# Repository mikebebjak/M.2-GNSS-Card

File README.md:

There are plenty of USB GNSS modules but very few M.2 modules for PCs. This project sought to rectify this issue by using a u-Blox M8C chip on a M.2 card. This way you can add GNSS to any PC when customers do not want to use external USB dongles. 
This card uses an HF4 antenna header for an external antenna (either direct or through a converter cable).
You can also download u-Blox software to test it out in Windows, as the attached screenshot shows.
Hopefully this helps someone!

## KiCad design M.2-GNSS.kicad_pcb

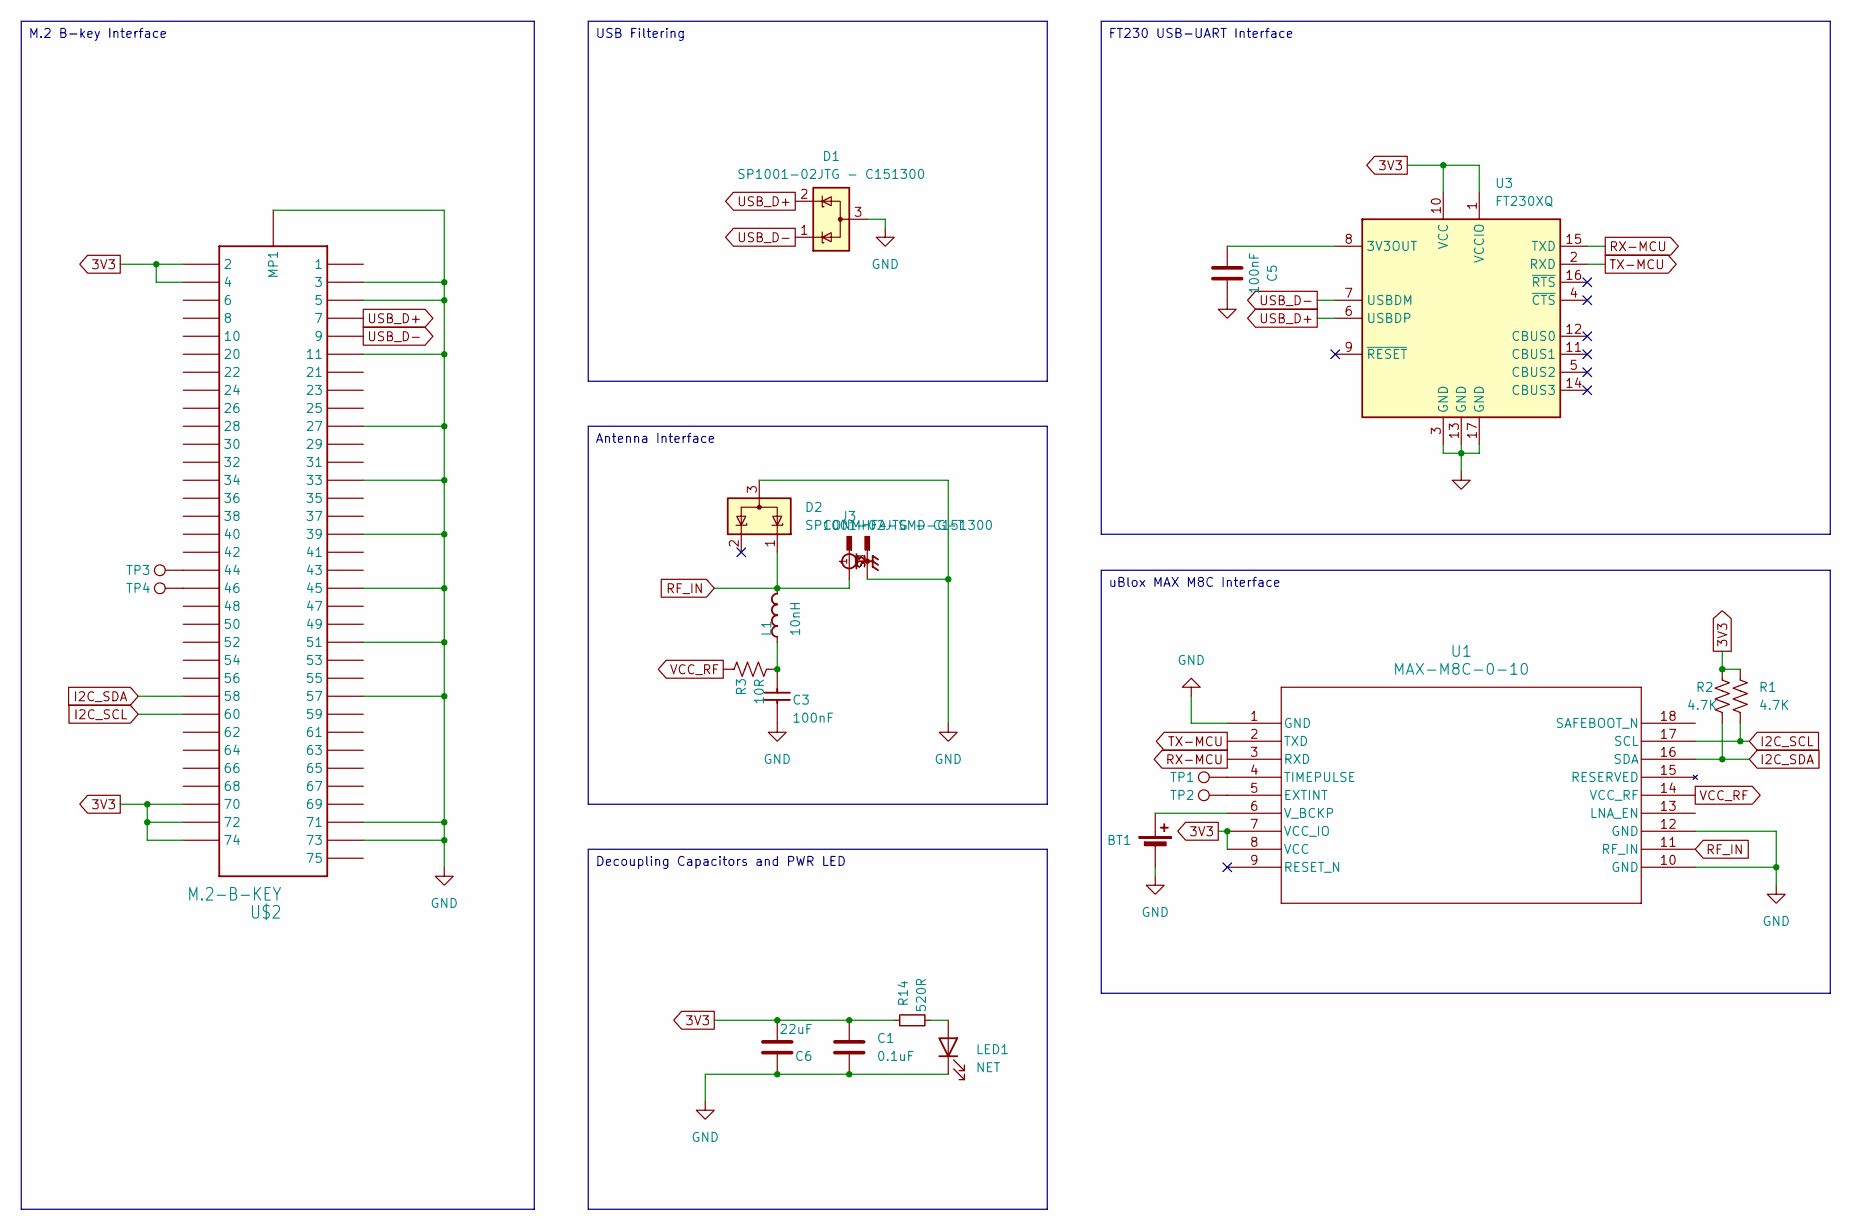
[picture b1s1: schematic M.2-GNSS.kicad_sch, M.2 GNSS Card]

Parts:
BT1: Battery_Cell; BAT_3030TR
C1: 0.1uF; C_0402_1005Metric
C3: 100nF; C_0402_1005Metric; PART NUMBER C0402-0.8p
C5: 100nF; C_0402_1005Metric
C6: 22uF; C_0603_1608Metric
D1, D2: SP1001-02JTG - C151300; SOT-323_SC-70
J3: CONMHF4-SMD-G-T; LINX_CONMHF4-SMD-G-T
L1: 10nH; C_0402_1005Metric_Pad0.74x0.62mm_HandSolder; PART NUMBER L0402-4n7
LED1: NET; LED_0402_1005Metric
R1, R2: 4.7K; R_0402_1005Metric
R3: 10R; R_0402_1005Metric
R14: 520R; R_0402_1005Metric
TP1: TIMEPULSE; TestPoint_Pad_D1.5mm
TP2: EXTINT; TestPoint_Pad_D1.5mm
TP3: GPIO2; TestPoint_Pad_D1.5mm
TP4: GPIO3; TestPoint_Pad_D1.5mm
U1: MAX-M8C-0-10; MAX-8&slash_MAX-M8_UBL
U3: FT230XQ; QFN-16-1EP_4x4mm_P0.65mm_EP2.1x2.1mm
U$2: M.2-B-KEY

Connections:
3V3: C1.2, C6.1, R1.1, R2.1, R14.1, U1.7 (VCC_IO), U1.8 (VCC), U3.1 (VCCIO), U3.10 (VCC), U$2.P$2 (2), U$2.P$4 (4), U$2.P$70 (70), U$2.P$72 (72), U$2.P$74 (74)
GND: BT1.2 (-), C1.1, C3.1, C5.1, C6.2, D1.3 (A), D2.3 (A), J3.S1, J3.S2, J3.S3, LED1.1 (K), U1.1 (GND), U1.10 (GND), U1.12 (GND), U3.3 (GND), U3.13 (GND), U3.17 (GND), U$2.MOUNTING-HOLE (MP1), U$2.P$3 (3), U$2.P$5 (5), U$2.P$11 (11), U$2.P$27 (27), U$2.P$33 (33), U$2.P$39 (39), U$2.P$45 (45), U$2.P$51 (51), U$2.P$57 (57), U$2.P$71 (71), U$2.P$73 (73); also elsewhere on the board
I2C_SCL: R1.2, U1.17 (SCL), U$2.P$60 (60)
I2C_SDA: R2.2, U1.16 (SDA), U$2.P$58 (58)
unnamed: BT1.1 (+), U1.6 (V_BCKP)
unnamed: C3.2, L1.1, R3.2
unnamed: LED1.2 (A), R14.2
unnamed: TP2.1, U1.5 (EXTINT)
unnamed: TP1.1, U1.4 (TIMEPULSE)
unnamed: C5.2, U3.8 (3V3OUT)
unnamed: TP3.1, U$2.P$44 (44)
unnamed: TP4.1, U$2.P$46 (46)
RF_IN: D2.1 (K), J3.1, L1.2, U1.11 (RF_IN); also elsewhere on the board
RX-MCU: U1.3 (RXD), U3.15 (TXD)
TX-MCU: U1.2 (TXD), U3.2 (RXD)
USB_D+: D1.2 (K), U3.6 (USBDP), U$2.P$7 (7)
USB_D-: D1.1 (K), U3.7 (USBDM), U$2.P$9 (9)
VCC_RF: R3.1, U1.14 (VCC_RF)

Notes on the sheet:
FT230 USB-UART Interface
Antenna Interface
M.2 B-key Interface
Decoupling Capacitors and PWR LED
USB Filtering
uBlox MAX M8C Interface

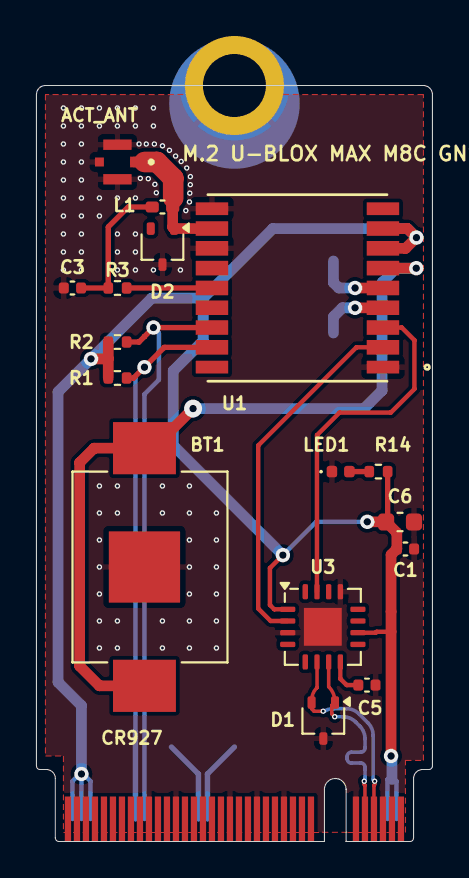
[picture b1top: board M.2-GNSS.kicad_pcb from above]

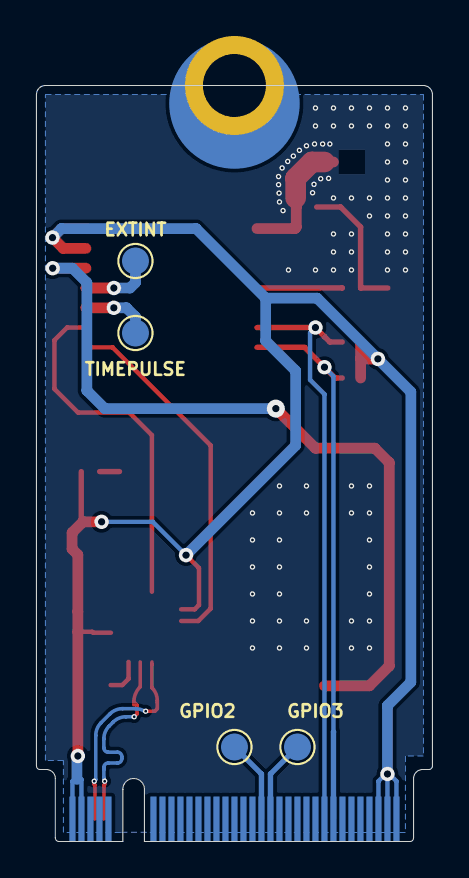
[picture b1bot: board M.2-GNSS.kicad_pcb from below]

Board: 2 copper layers, 22.0 x 42.0 mm, 21 parts (4 on the bottom side), 18 nets.

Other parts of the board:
ACT_ANT: CONMHF4-SMD-G-T; LINX_CONMHF4-SMD-G-T

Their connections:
GND: ACT_ANT.S1, ACT_ANT.S2, ACT_ANT.S3; also elsewhere on the board
RF_IN: ACT_ANT.1; also elsewhere on the board

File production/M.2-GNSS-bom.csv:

Comment,Designator,Footprint,JLCPCB Part #
SP1001-02JTG,"D1,D2",SOT-323_SC-70,C151300
FT230XQ,U3,QFN-16-1EP_4x4mm_P0.65mm_EP2.1x2.1mm,C128629
100nF,"C5,C3",C_0402_1005Metric,C1525 
Battery_Cell,BT1,BAT_3030TR,
520R,R14,R_0402_1005Metric,C365029
NET,LED1,LED_0402_1005Metric,
10R,R3,R_0402_1005Metric,
4.7K,"R2,R1",R_0402_1005Metric,
22uF,C6,C_0603_1608Metric,
0.1uF,C1,C_0402_1005Metric,C1525 
10nH,L1,C_0402_1005Metric_Pad0.74x0.62mm_HandSolder,
CONMHF4-SMD-G-T,ACT_ANT,LINX_CONMHF4-SMD-G-T,C18221168
MAX-M8C-0-10,U1,MAX-8 MAX-M8_UBL,

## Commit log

2025-12-10 Update README.md
    added photo
